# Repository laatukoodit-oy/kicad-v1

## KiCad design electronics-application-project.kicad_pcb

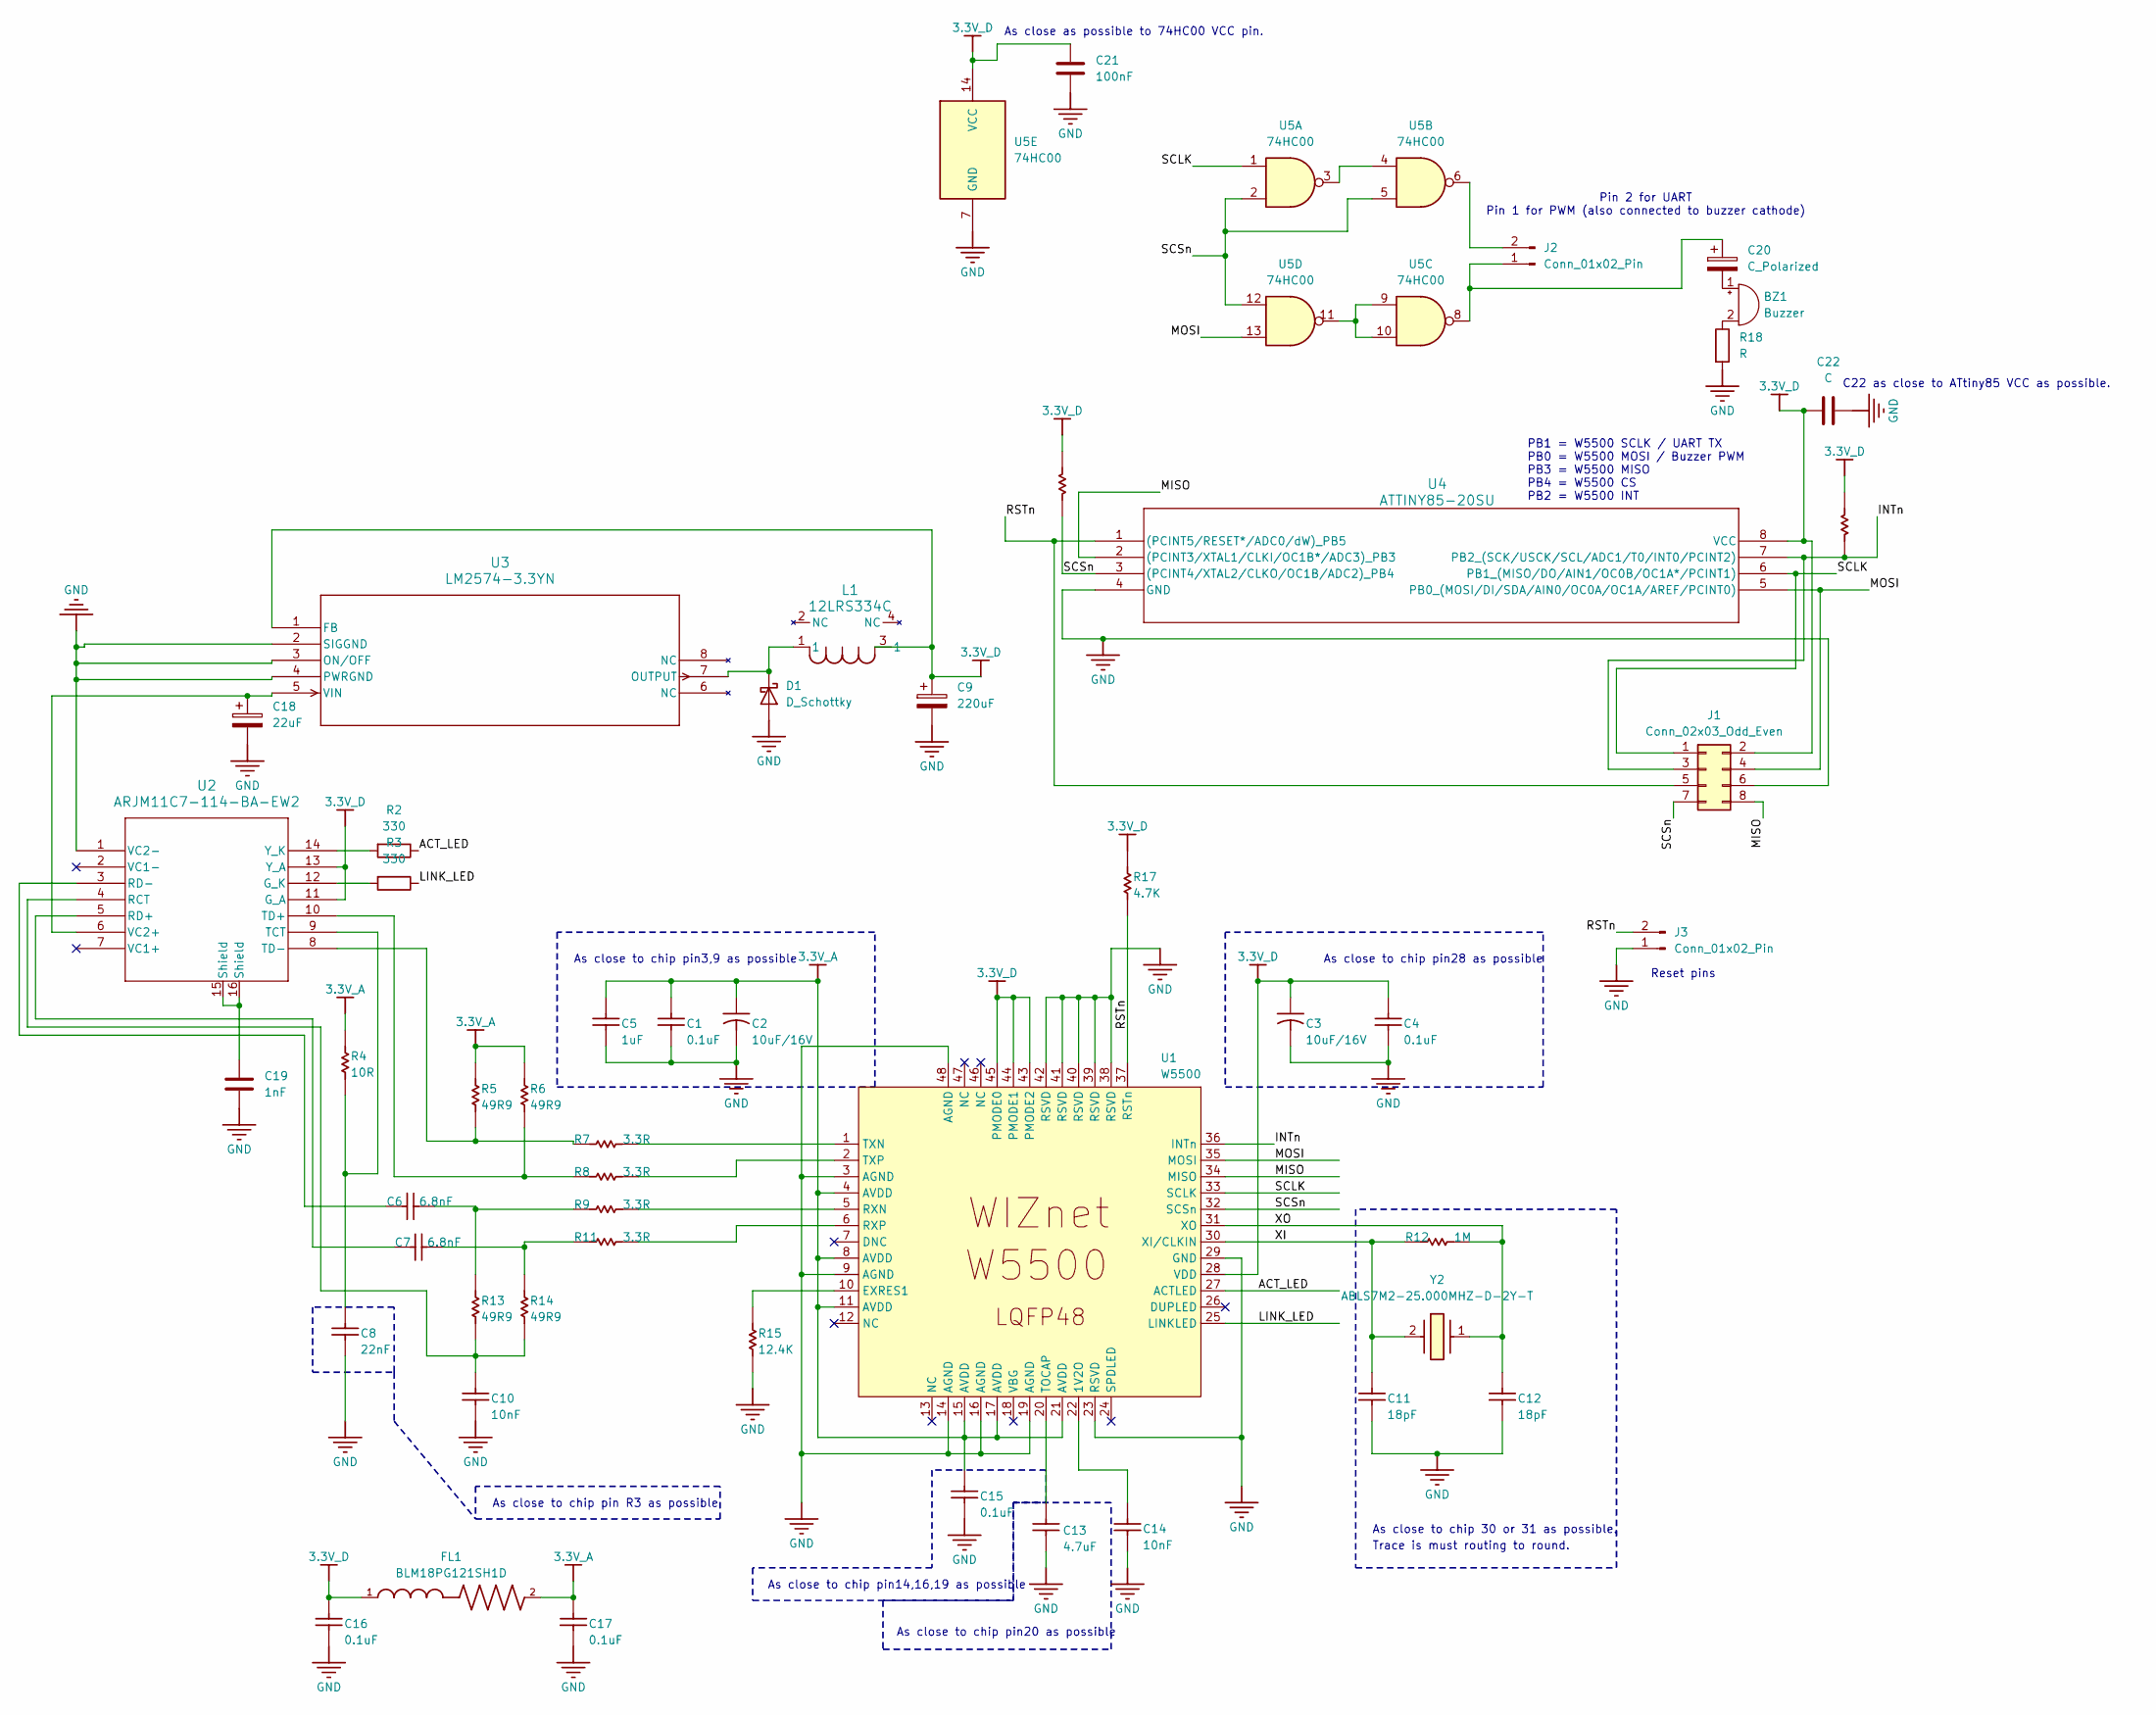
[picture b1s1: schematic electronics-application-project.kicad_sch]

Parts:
BZ1: Buzzer; Buzzer_12x9.5RM7.6
C1, C4, C15, C16, C17: 0.1uF; C_0805_2012Metric_Pad1.18x1.45mm_HandSolder
C2, C3: 10uF/16V; C_1206_3216Metric_Pad1.33x1.80mm_HandSolder
C5: 1uF; C_0805_2012Metric_Pad1.18x1.45mm_HandSolder
C6, C7: 6.8nF; C_0805_2012Metric_Pad1.18x1.45mm_HandSolder
C8: 22nF; C_0805_2012Metric_Pad1.18x1.45mm_HandSolder
C9: 220uF; CP_Elec_8x6.2
C10, C14: 10nF; C_0805_2012Metric_Pad1.18x1.45mm_HandSolder
C11, C12: 18pF; C_0805_2012Metric_Pad1.18x1.45mm_HandSolder
C13: 4.7uF; C_0805_2012Metric_Pad1.18x1.45mm_HandSolder
C18: 22uF; CP_Elec_6.3x5.4
C19: 1nF; C_1210_3225Metric_Pad1.33x2.70mm_HandSolder
C20: C_Polarized; C_0805_2012Metric_Pad1.18x1.45mm_HandSolder
C21: 100nF; C_0805_2012Metric_Pad1.18x1.45mm_HandSolder
C22: C; C_0805_2012Metric_Pad1.18x1.45mm_HandSolder
D1: D_Schottky; Nexperia_CFP3_SOD-123W
FL1: BLM18PG121SH1D; BEADC1608X95N
J1: Conn_02x03_Odd_Even; PinHeader_2x04_P2.54mm_Vertical
J2, J3: Conn_01x02_Pin; PinHeader_1x02_P2.54mm_Vertical
L1: 12LRS334C; IND_MURATA_1200LRS_MUR
R1, R10, R17: 4.7K; R_0805_2012Metric_Pad1.20x1.40mm_HandSolder
R2, R3: 330; R_0805_2012Metric_Pad1.20x1.40mm_HandSolder
R4: 10R; R_0805_2012Metric_Pad1.20x1.40mm_HandSolder
R5, R6, R13, R14: 49R9; R_0805_2012Metric_Pad1.20x1.40mm_HandSolder
R7, R8, R9, R11: 3.3R; R_0805_2012Metric_Pad1.20x1.40mm_HandSolder
R12: 1M; R_0805_2012Metric_Pad1.20x1.40mm_HandSolder
R15: 12.4K; R_0805_2012Metric_Pad1.20x1.40mm_HandSolder
R18: R; R_0805_2012Metric_Pad1.20x1.40mm_HandSolder
U1: W5500; 48LQFP_W5500_WIZ
U2: ARJM11C7-114-BA-EW2; ARJM11C7-114-BA-EW2_ABR-fixed
U3: LM2574-3.3YN; PDIP-8_MCL
U4: ATTINY85-20SU; 8S2_ATM
U5: 74HC00; SO-14_3.9x8.65mm_P1.27mm
Y2: ABLS7M2-25.000MHZ-D-2Y-T; ABLS7M225000MHZD2YT; Mouser Part Number 815-ABLS7M2-25D2YT

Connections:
3.3V_A: C1.2, C2.1, C5.2, C15.2, C17.2, FL1.2, R4.2, R5.2, R6.2, U1.4 (AVDD), U1.8 (AVDD), U1.11 (AVDD), U1.15 (AVDD), U1.17 (AVDD), U1.21 (AVDD)
3.3V_D: C3.1, C4.2, C9.1, C16.2, C21.1, C22.2, FL1.1, J1.2, L1.3 (1), R1.2, R10.2, R17.2, U1.28 (VDD), U1.43 (PMODE2), U1.44 (PMODE1), U1.45 (PMODE0), U2.11 (G_A), U2.13 (Y_A), U3.1 (FB), U4.8 (VCC), U5.14 (VCC)
/ACT_LED: R2.1, U1.27 (ACTLED)
/INTn: J1.3, R1.1, U1.36 (INTn), U4.7 (PB2_(SCK/USCK/SCL/ADC1/T0/INT0/PCINT2))
/LINK_LED: R3.1, U1.25 (LINKLED)
/MISO: J1.8, U1.34 (MISO), U4.2 ((PCINT3/XTAL1/CLKI/OC1B*/ADC3)_PB3)
/MOSI: J1.4, U1.35 (MOSI), U4.5 (PB0_(MOSI/DI/SDA/AIN0/OC0A/OC1A/AREF/PC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), U5.13
/RSTn: J1.5, J3.2, R17.1, U1.37 (RSTn), U4.1 ((PCINT5/RESET*/ADC0/dW)_PB5)
/SCLK: J1.1, U1.33 (SCLK), U4.6 (PB1_(MISO/DO/AIN1/OC0B/OC1A*/PCINT1)), U5.1
/SCSn: J1.7, R10.1, U1.32 (SCSn), U4.3 ((PCINT4/XTAL2/CLKO/OC1B/ADC2)_PB4), U5.2, U5.5, U5.12
/XI: C11.2, R12.1, U1.30 (XI/CLKIN), Y2.2 (CRYSTAL_2)
/XO: C12.2, R12.2, U1.31 (XO), Y2.1
GND: C1.1, C2.2, C3.2, C4.1, C5.1, C8.1, C9.2, C10.1, C11.1, C12.1, C13.1, C14.1, C15.1, C16.1, C17.1, C18.2, C19.2, C21.2, C22.1, D1.2 (A), J1.6, J3.1, R15.1, R18.2, U1.3 (AGND), U1.9 (AGND), U1.14 (AGND), U1.16 (AGND), U1.19 (AGND), U1.23 (RSVD), U1.29 (GND), U1.38 (RSVD), U1.39 (RSVD), U1.40 (RSVD), U1.41 (RSVD), U1.42 (RSVD), U1.48 (AGND), U2.1 (VC2-), U3.2 (SIGGND), U3.3 (ON/OFF), U3.4 (PWRGND), U4.4 (GND), U5.7 (GND)
unnamed: BZ1.1 (+), C20.2
unnamed: BZ1.2 (-), R18.1
unnamed: C6.2, R9.1, R13.2
unnamed: C7.2, R11.1, R14.2
unnamed: C19.1, U2.15 (Shield), U2.16 (Shield)
unnamed: D1.1 (K), L1.1, U3.7 (OUTPUT)
unnamed: C20.1, J2.1, U5.8
unnamed: J2.2, U5.6
unnamed: C14.2, U1.22 (1V2O)
unnamed: R15.2, U1.10 (EXRES1)
unnamed: R9.2, U1.5 (RXN)
unnamed: R11.2, U1.6 (RXP)
unnamed: C13.2, U1.20 (TOCAP)
unnamed: R7.2, U1.1 (TXN)
unnamed: R8.2, U1.2 (TXP)
unnamed: R3.2, U2.12 (G_K)
unnamed: C10.2, R13.1, R14.1, U2.4 (RCT)
unnamed: C7.1, U2.5 (RD+)
unnamed: C6.1, U2.3 (RD-)
unnamed: C8.2, R4.1, U2.9 (TCT)
unnamed: R6.1, R8.1, U2.10 (TD+)
unnamed: R5.1, R7.1, U2.8 (TD-)
unnamed: C18.1, U2.6 (VC2+), U3.5 (VIN)
unnamed: R2.2, U2.14 (Y_K)
unnamed: U5.3, U5.4
unnamed: U5.9, U5.10, U5.11

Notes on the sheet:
As close to chip 30 or 31 as possible.
PB1 = W5500 SCLK / UART TX PB0 = W5500 MOSI / Buzzer PWM PB3 = W5500 MISO PB4 = W5500 CS PB2 = W5500 INT
Pin 2 for UART Pin 1 for PWM (also connected to buzzer cathode)
As close to chip pin20 as possible
Reset pins
As close as possible to 74HC00 VCC pin.
As close to chip pin28 as possible
As close to chip pin14,16,19 as possible
Trace is must routing to round.
C22 as close to ATtiny85 VCC as possible.
As close to chip pin R3 as possible
As close to chip pin3,9 as possible

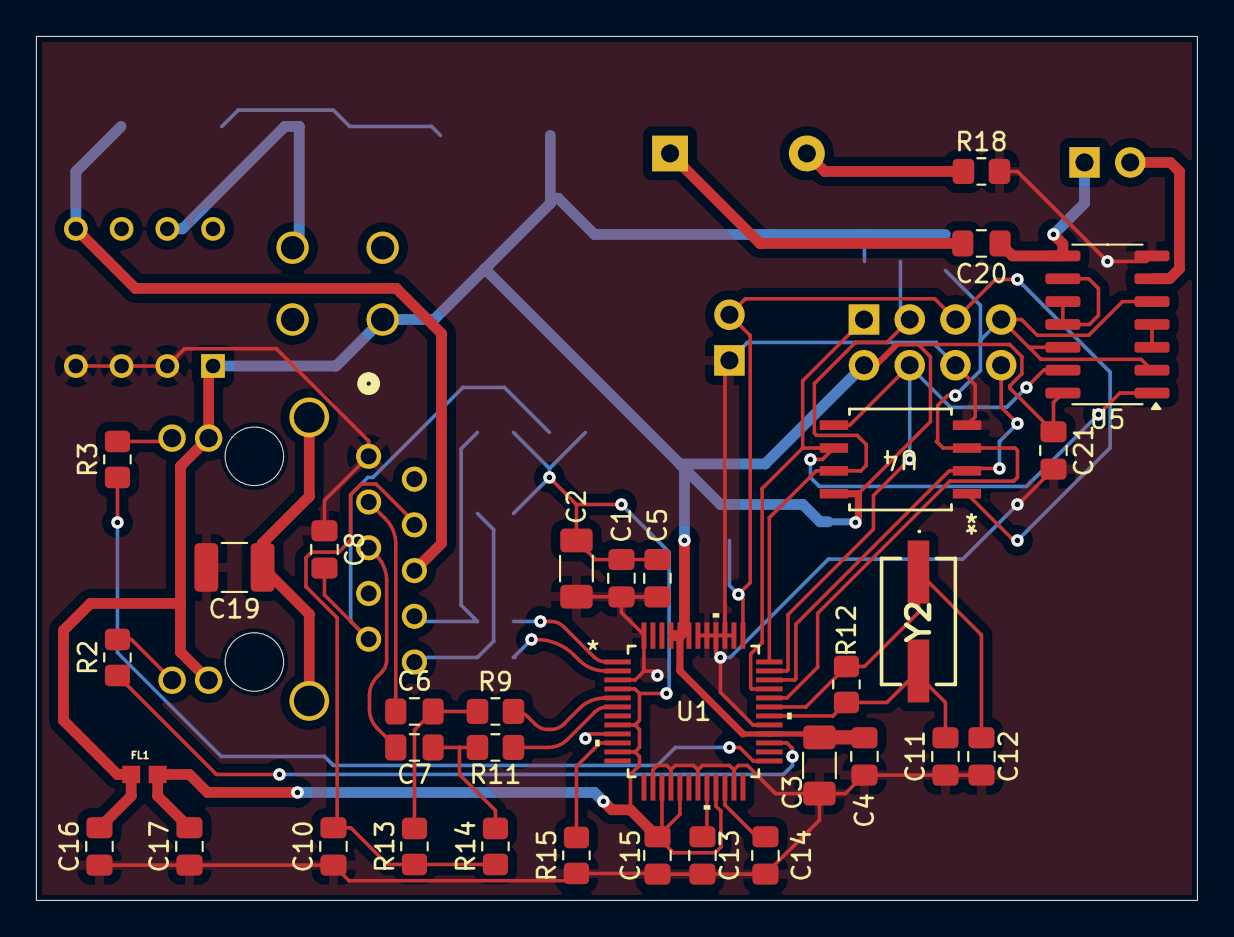
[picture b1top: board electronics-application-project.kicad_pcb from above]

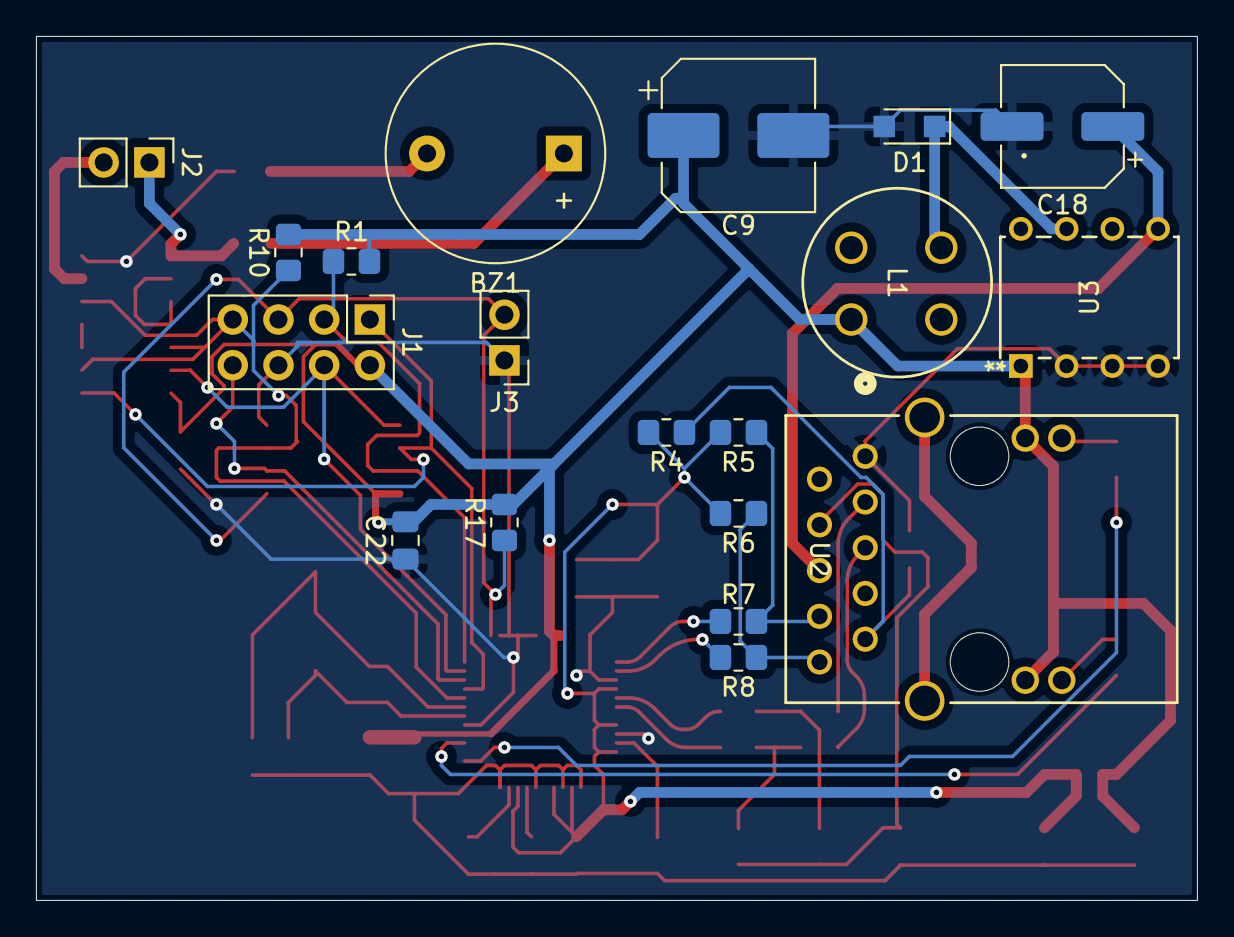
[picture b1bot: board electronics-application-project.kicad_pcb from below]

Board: 2 copper layers, 64.5 x 48.0 mm, 52 parts (19 on the bottom side), 39 nets.

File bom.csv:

"Reference","Value","Datasheet","Footprint","Qty","DNP"
"C1,C4,C15,C16,C17","0.1uF","","Capacitor_SMD:C_0805_2012Metric_Pad1.18x1.45mm_HandSolder","5",""
"C2,C3","10uF/16V","","Capacitor_SMD:C_1206_3216Metric_Pad1.33x1.80mm_HandSolder","2",""
"C5","1uF","","Capacitor_SMD:C_0805_2012Metric_Pad1.18x1.45mm_HandSolder","1",""
"C6,C7","6.8nF","","Capacitor_SMD:C_0805_2012Metric_Pad1.18x1.45mm_HandSolder","2",""
"C8","22nF","","Capacitor_SMD:C_0805_2012Metric_Pad1.18x1.45mm_HandSolder","1",""
"C9","220uF","~","Capacitor_SMD:CP_Elec_8x6.2","1",""
"C10,C14","10nF","","Capacitor_SMD:C_0805_2012Metric_Pad1.18x1.45mm_HandSolder","2",""
"C11,C12","18pF","","Capacitor_SMD:C_0805_2012Metric_Pad1.18x1.45mm_HandSolder","2",""
"C13","4.7uF","","Capacitor_SMD:C_0805_2012Metric_Pad1.18x1.45mm_HandSolder","1",""
"C18","22uF","~","Capacitor_SMD:CP_Elec_6.3x5.4","1",""
"C19","1nF","~","Capacitor_SMD:C_1210_3225Metric_Pad1.33x2.70mm_HandSolder","1",""
"D1","D_Schottky","~","Diode_SMD:Nexperia_CFP3_SOD-123W","1",""
"FL1","BLM18PG121SH1D","","Imported:BEADC1608X95N","1",""
"J1","Conn_02x03_Odd_Even","~","Connector_PinHeader_2.54mm:PinHeader_2x03_P2.54mm_Vertical","1",""
"L1","12LRS334C","12LRS334C","Imported:IND_MURATA_1200LRS_MUR","1",""
"R1,R10,R16,R17","4.7K","","Resistor_SMD:R_0805_2012Metric_Pad1.20x1.40mm_HandSolder","4",""
"R2,R3","330","~","Resistor_SMD:R_0805_2012Metric_Pad1.20x1.40mm_HandSolder","2",""
"R4","10R","","Resistor_SMD:R_0805_2012Metric_Pad1.20x1.40mm_HandSolder","1",""
"R5,R6,R13,R14","49R9","","Resistor_SMD:R_0805_2012Metric_Pad1.20x1.40mm_HandSolder","4",""
"R7,R8,R9,R11","3.3R","","Resistor_SMD:R_0805_2012Metric_Pad1.20x1.40mm_HandSolder","4",""
"R12","1M","","Resistor_SMD:R_0805_2012Metric_Pad1.20x1.40mm_HandSolder","1",""
"R15","12.4K","","Resistor_SMD:R_0805_2012Metric_Pad1.20x1.40mm_HandSolder","1",""
"U1","W5500","","Imported:48LQFP_W5500_WIZ","1",""
"U2","ARJM11C7-114-BA-EW2","ARJM11C7-114-BA-EW2","Imported:ARJM11C7-114-BA-EW2_ABR-fixed","1",""
"U3","LM2574-3.3YN","LM2574-3.3YN","Imported:PDIP-8_MCL","1",""
"U4","ATTINY85-20SU","ATTINY85-20SU","Imported:8S2_ATM","1",""
"Y2","ABLS7M2-25.000MHZ-D-2Y-T","http://abracon.com/Resonators/ABLS7M2.pdf","Imported:ABLS7M225000MHZD2YT","1",""

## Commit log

2025-03-25 add ethernet leds; change power supply capacitors; change attiny85 pin connections;
2025-03-25 update schematic to readme; remove unfinished layout from readme;
2025-03-26 start over
2025-03-27 pcb progress
2025-03-28 add NAND gates and a pin header for UART and PWM; add buzzer; add pin header for GND and 3.3V_D; expand ATtiny85 pin header to all pins; join W5500 RST and ATtiny85 RST and add a pin header for the n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
2025-03-28 connect attiny85 to GND and 3.3V_D rails; remove redundant pin header;
2025-03-28 update pcb from schematic
2025-03-30 pcb done, but has some errors still
2025-03-31 flip buzzer to back side
2025-03-31 gnd issue fixed
2025-03-31 DRC pass
2025-03-31 remove redundant header from layout
2025-03-31 shrinking of the board
2025-03-31 ship it
